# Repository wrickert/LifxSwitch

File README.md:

Hardware Capacitive Touch Smartlight Switch

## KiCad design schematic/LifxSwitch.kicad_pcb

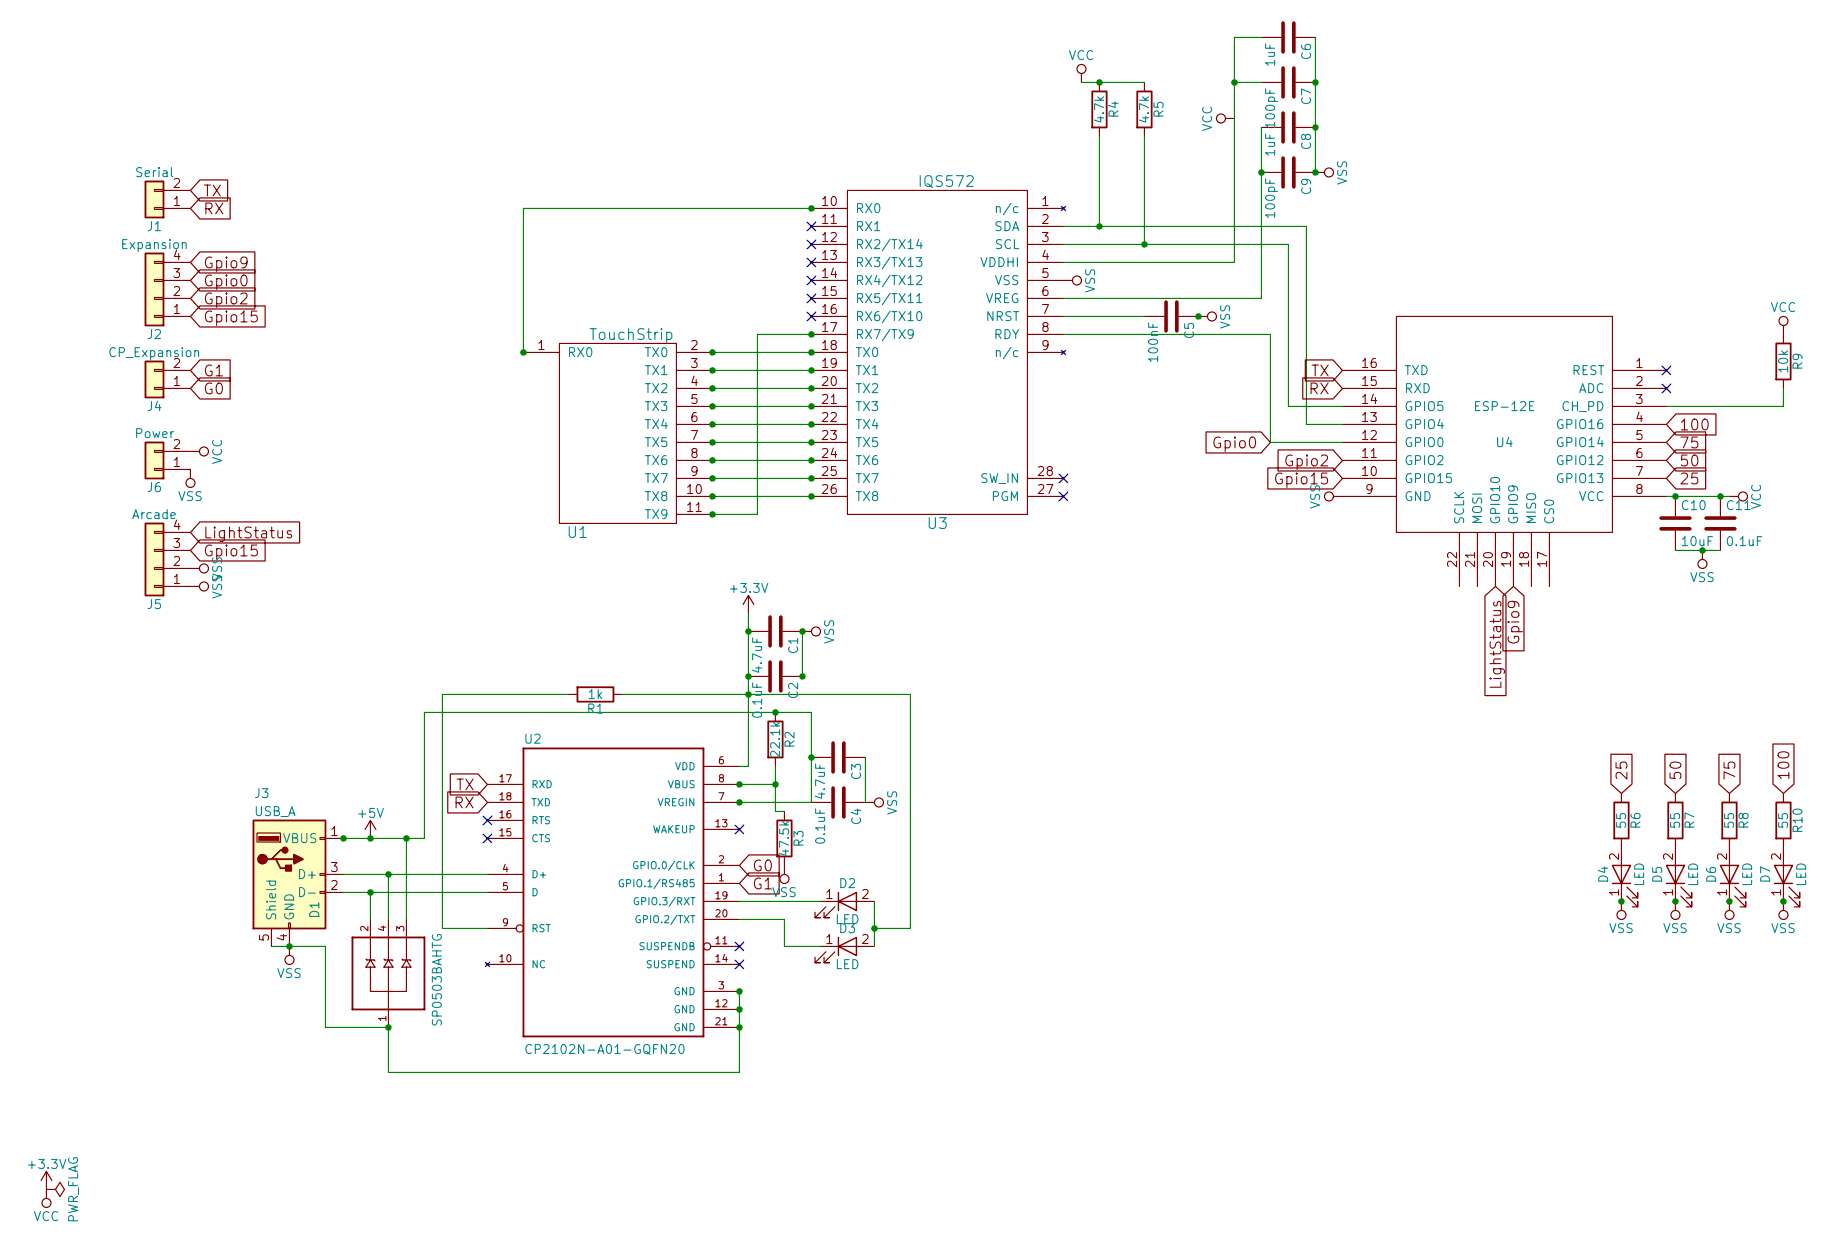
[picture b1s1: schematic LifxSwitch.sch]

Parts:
C1, C3: 4.7uF; C_0805
C2, C4, C11: 0.1uF; C_0805
C5: 100nF; C_0805
C6, C8: 1uF; C_0805
C7, C9: 100pF; C_0805
C10: 10uF; C_0805
D1: SP0503BAHTG; SOT192P237X122-4N
D2, D3, D4, D5, D6, D7: LED; LED_0805
J1: Serial; Pin_Header_Straight_1x02_Pitch2.54mm
J2: Expansion; Pin_Header_Straight_1x04_Pitch2.54mm
J3: USB_A; USB_Micro-B_Molex_47346-0001
J4: CP_Expansion; Pin_Header_Straight_1x02_Pitch2.54mm
J5: Arcade; Pin_Header_Straight_1x04_Pitch2.54mm
J6: Power; Pin_Header_Straight_1x02_Pitch2.54mm
R1: 1k; R_0805
R2: 22.1k; R_0805
R3: 47.5k; R_0805
R4, R5: 4.7k; R_0805
R6, R7, R8, R10: 55; R_0805
R9: 10k; R_0805
U1: TouchStrip; Touchstrip
U2: CP2102N-A01-GQFN20; SILABS_QFN20
U3: IQS572; QFN-28-1EP_4x4mm_Pitch0.4mm-Without-Center-Pads
U4: ESP-12E

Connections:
25: R6.1, U4.7 (GPIO13)
50: R7.1, U4.6 (GPIO12)
75: R8.1, U4.5 (GPIO14)
100: R10.1, U4.4 (GPIO16)
+5V: C3.2, C4.2, D1.3 (B), J3.1 (VBUS), R2.1, U2.7 (VREGIN)
G0: J4.1, U2.2 (GPIO.0/CLK)
G1: J4.2, U2.1 (GPIO.1/RS485)
Gpio0: J2.3, U3.8 (RDY), U4.12 (GPIO0)
Gpio2: J2.2, U4.11 (GPIO2)
Gpio9: J2.4, U4.19 (GPIO9)
Gpio15: J2.1, J5.3, U4.10 (GPIO15)
LightStatus: J5.4, U4.20 (GPIO10)
unnamed: C5.2, U3.7 (NRST)
unnamed: C8.2, C9.2, U3.6 (VREG)
unnamed: D1.2 (A), J3.2 (D-), U2.5 (D)
unnamed: D1.4 (C), J3.3 (D+), U2.4 (D+)
unnamed 16: D2.1 (K), U2.19 (GPIO.3/RXT); also elsewhere on the board
unnamed 17: D3.1 (K), U2.20 (GPIO.2/TXT); also elsewhere on the board
unnamed: D4.2 (A), R6.2
unnamed: D5.2 (A), R7.2
unnamed: D6.2 (A), R8.2
unnamed: D7.2 (A), R10.2
unnamed: R1.2, U2.9 (RST)
unnamed: R2.2, R3.1, U2.8 (VBUS)
unnamed: R4.2, U3.2 (SDA), U4.13 (GPIO4)
unnamed: R5.2, U3.3 (SCL), U4.14 (GPIO5)
unnamed: R9.2, U4.3 (CH_PD)
unnamed 27: U1.1 (RX0), U3.10 (RX0); also elsewhere on the board
unnamed 28: U1.2 (TX0), U3.18 (TX0); also elsewhere on the board
unnamed 29: U1.3 (TX1), U3.19 (TX1); also elsewhere on the board
unnamed 30: U1.4 (TX2), U3.20 (TX2); also elsewhere on the board
unnamed 31: U1.5 (TX3), U3.21 (TX3); also elsewhere on the board
unnamed 32: U1.6 (TX4), U3.22 (TX4); also elsewhere on the board
unnamed 33: U1.7 (TX5), U3.23 (TX5); also elsewhere on the board
unnamed 34: U1.8 (TX6), U3.24 (TX6); also elsewhere on the board
unnamed 35: U1.9 (TX7), U3.25 (TX7); also elsewhere on the board
unnamed 36: U1.10 (TX8), U3.26 (TX8); also elsewhere on the board
unnamed 37: U1.11 (TX9), U3.17 (RX7/TX9); also elsewhere on the board
RX: J1.1, U2.18 (TXD), U4.15 (RXD)
TX: J1.2, U2.17 (RXD), U4.16 (TXD)
VSS: C1.1, C2.1, C3.1, C4.1, C5.1, C6.1, C7.1, C8.1, C9.1, C10.2, C11.2, D1.1 (GND), D4.1 (K), D5.1 (K), D6.1 (K), D7.1 (K), J3.4 (GND), J3.5 (Shield), J5.1, J5.2, J6.1, R3.2, U2.3 (GND), U2.12 (GND), U2.21 (GND), U3.5 (VSS), U4.9 (GND)

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
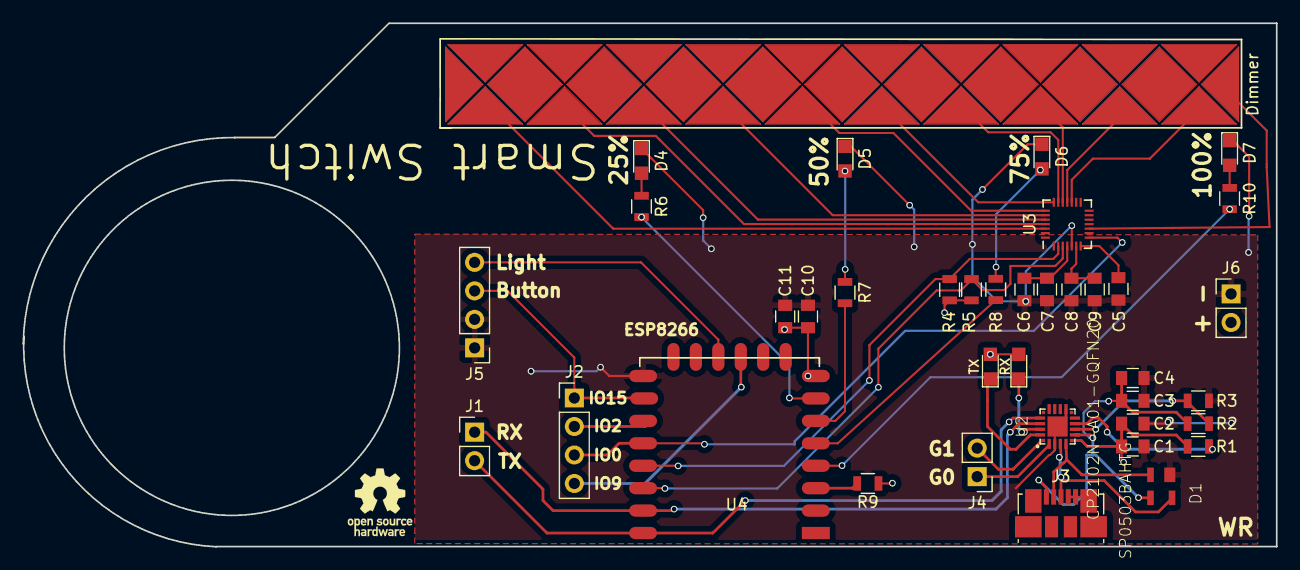
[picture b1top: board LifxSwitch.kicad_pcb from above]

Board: 2 copper layers, 111.7 x 46.7 mm, 38 parts (0 on the bottom side), 43 nets.

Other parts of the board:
Dimmer: TouchStrip; Touchstrip
RX: LED; LED_0805
TX: LED; LED_0805

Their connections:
unnamed 16: RX.1; also elsewhere on the board
unnamed 17: TX.1; also elsewhere on the board
unnamed 27: Dimmer.36; also elsewhere on the board
unnamed 28: Dimmer.26; also elsewhere on the board
unnamed 29: Dimmer.28; also elsewhere on the board
unnamed 30: Dimmer.29; also elsewhere on the board
unnamed 31: Dimmer.30; also elsewhere on the board
unnamed 32: Dimmer.31; also elsewhere on the board
unnamed 33: Dimmer.32; also elsewhere on the board
unnamed 34: Dimmer.33; also elsewhere on the board
unnamed 35: Dimmer.34; also elsewhere on the board
unnamed 36: Dimmer.35; also elsewhere on the board
unnamed 37: Dimmer.27; also elsewhere on the board

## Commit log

2018-06-20 Added readme
2018-06-20 Added some wires and pads
2018-06-20 Put some values in so I dont have to look them up later
2018-06-20 something
2018-06-24 Added folder structure
2018-06-25 Completed Schematic
2018-06-26 Completed PCB layout
2018-06-29 Finished V1 schematic
2018-07-13 Fixed dimmer footprint
2018-09-05 Updating
